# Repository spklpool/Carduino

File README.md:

# Carduino

This repository contains the source code for the Carduino library for Arduino IDE as well as design files for the electronics and the 3d printed enclosure for the Carduino device.  Each of these 3 components will be desctibed separately below.  More information about Carduino can be found at https://carduino.co

Everything you need to build a Carduino is in this repository if you have the necessary equipment.  If you are so inclined, you scan shop around for all the parts and build one yourself using the information you find in here.  You can also order a kit with all the electronic parts from our store at
https://www.tindie.com/stores/Sparkle/

There, you can also order one fully assembled and tested, including the 3d printed enclosure and a USB cable for close to the same price it would cost you to buy all the individual parts and the shipping costs.  Also, buying from our store helps support the continuing development of the project.  We have other things in the works you might like if you're interested in Cardano and electronics.

## Arduino library
The Arduino IDE can be downloaded here:
https://www.arduino.cc/en/software
The files that make up the library are under the src folder for reference if you want to look at the code.  To use it though, you'll want to install it as a library in the IDE.  Instructions for installing the library and everything else you need to program your Carduino can be found in this tutorial video:
https://www.youtube.com/watch?v=BPkC6jxjeJc&t=7s

## PCB design files
The PCB is designed using Eagle.  It meets the criteria for being edited using the free edition for personal use, which can be downloaded here:
https://www.autodesk.ca/en/products/eagle/free-download
The PCB design files can be found in the eagle folder.
The parts list with recommended manufacturer part numbers is available in the [parts file](eagle/parts.md)

## Enclosure 3d model
The enclosure was designed with TinkerCad.  Unfortunately, TimcarCad does not support saving the native files, but the exported .stl files can be imported and tweaked as you wish at:
https://www.tinkercad.com/
The 3d model files can be found in the model folder.

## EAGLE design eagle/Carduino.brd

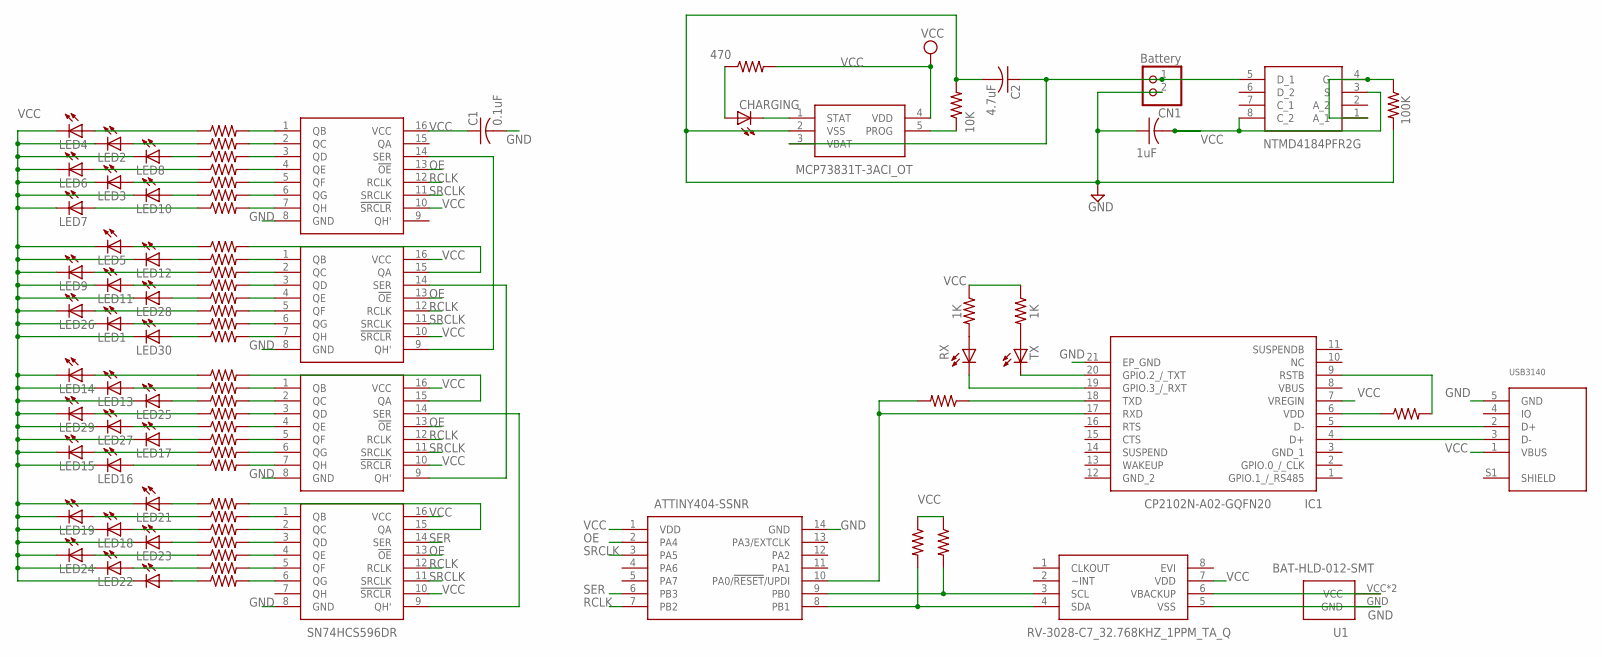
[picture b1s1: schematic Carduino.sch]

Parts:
C1: 0.1uF; C1206
C2: 4.7uF; C1206
C3: 1uF; C1206
CHARGING: Red; CHIP-LED0805
CN1: Battery; JST-PH-2-SMT-RA
IC1: CP2102N-A02-GQFN20; CP2102NA02GQFN20
IC3, IC4, IC5, IC6: SN74HCS596DR; SOIC127P600X175-16N
IC7: NTMD4184PFR2G; SOIC127P600X175-8N
IC8: ATTINY404-SSNR; SOIC127P600X175-14N
IC9: MCP73831T-3ACI_OT; SOT95P270X145-5N
IC11: RV-3028-C7_32.768KHZ_1PPM_TA_Q; RV3028C732768KHZ1PPMTAQC
LED1, LED2, LED3, LED4, LED5, LED6, LED7, LED8, LED9, LED10, LED11, LED12, LED13, LED14, LED15, LED16, LED17, LED18, LED19, LED20, LED21, LED22, LED23, LED24, LED25, LED26, LED27, LED28, LED29, LED30: LUXEON2835L128-1890NA3500001; LUXEON2835
R1, R16: 470; R0805
R2, R3, R7, R8, R9, R10, R11, R12, R13, R14, R15, R17, R18, R19, R20, R23, R31, R32, R33, R34, R35, R36, R37, R38, R39, R40, R41, R42, R43, R44, R45, R46, R47: 1K; R0805
R4, R5: 4.7K; R0805
R21: 100K; R0805
R22: 10K; R0805
RX: Green; CHIP-LED0805
TX: Red; CHIP-LED0805
U1: BAT-HLD-012-SMT; BATHLD012SMT
U$5: USB3140; USB3140-30-0170-0-C

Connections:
GND: C1.2, C2.2, C3.1, CN1.2 (1), IC1.21 (EP_GND), IC3.8 (GND), IC4.8 (GND), IC5.8 (GND), IC6.8 (GND), IC8.14 (GND), IC9.2 (VSS), IC11.5 (VSS), R21.2, R22.2, U1.GND, U$5.5 (GND)
unnamed: LED4.ANODE (A), R15.1
unnamed: LED2.ANODE (A), R14.1
unnamed: LED8.ANODE (A), R13.1
unnamed: LED6.ANODE (A), R12.1
unnamed: LED3.ANODE (A), R11.1
unnamed: LED12.ANODE (A), R7.1
unnamed: LED7.ANODE (A), R9.1
unnamed: LED5.ANODE (A), R8.1
unnamed: LED10.ANODE (A), R10.1
unnamed: LED9.ANODE (A), R17.1
unnamed: LED11.ANODE (A), R18.1
unnamed: LED28.ANODE (A), R19.1
unnamed: LED26.ANODE (A), R20.1
unnamed: LED1.ANODE (A), R31.1
unnamed: LED30.ANODE (A), R32.1
unnamed: LED14.ANODE (A), R33.1
unnamed: LED13.ANODE (A), R34.1
unnamed: LED25.ANODE (A), R35.1
unnamed: LED29.ANODE (A), R36.1
unnamed: LED27.ANODE (A), R37.1
unnamed: LED17.ANODE (A), R38.1
unnamed: LED15.ANODE (A), R39.1
unnamed: LED16.ANODE (A), R40.1
unnamed: LED21.ANODE (A), R41.1
unnamed: LED19.ANODE (A), R42.1
unnamed: LED18.ANODE (A), R43.1
unnamed: LED23.ANODE (A), R44.1
unnamed: LED24.ANODE (A), R45.1
unnamed: LED22.ANODE (A), R46.1
unnamed: LED20.ANODE (A), R47.1
unnamed: IC8.8 (PB1), IC11.4 (SDA), R4.2
unnamed: IC8.9 (PB0), IC11.3 (SCL), R5.2
unnamed: IC11.6 (VBACKUP), U1.VCC, U1.VCC2 (VCC)
unnamed: IC7.1 (A_1), IC7.4 (G), R21.1
unnamed: IC9.5 (PROG), R22.1
unnamed: C2.1, CN1.1 (2), IC7.5 (D_1), IC9.3 (VBAT)
unnamed: CHARGING.C, IC9.1 (STAT)
unnamed: CHARGING.A, R16.1
unnamed: IC1.20 (GPIO.2_/_TXT), TX.C
unnamed: IC1.19 (GPIO.3_/_RXT), RX.C
unnamed: IC1.18 (TXD), R1.1
unnamed: IC1.6 (VDD), R23.1
unnamed: IC1.9 (RSTB), R23.2
unnamed: IC3.1 (QB), R15.2
unnamed: IC3.2 (QC), R14.2
unnamed: IC3.3 (QD), R13.2
unnamed: IC3.4 (QE), R12.2
unnamed: IC3.5 (QF), R11.2
unnamed: IC3.6 (QG), R10.2
unnamed: IC3.7 (QH), R9.2
unnamed: IC4.15 (QA), R8.2
unnamed: IC4.1 (QB), R7.2
unnamed: IC4.2 (QC), R17.2
unnamed: IC4.3 (QD), R18.2
unnamed: IC4.4 (QE), R19.2
unnamed: IC4.5 (QF), R20.2
unnamed: IC4.6 (QG), R31.2
unnamed: IC4.7 (QH), R32.2
unnamed: IC5.15 (QA), R33.2
unnamed: IC5.1 (QB), R34.2
unnamed: IC5.2 (QC), R35.2
unnamed: IC5.3 (QD), R36.2
unnamed: IC5.4 (QE), R37.2
unnamed: IC5.5 (QF), R38.2
unnamed: IC5.6 (QG), R39.2
unnamed: IC5.7 (QH), R40.2
unnamed: IC6.6 (QG), R47.2
unnamed: IC6.5 (QF), R46.2
unnamed: IC6.4 (QE), R45.2
unnamed: IC6.3 (QD), R44.2
unnamed: IC6.2 (QC), R43.2
unnamed: IC6.1 (QB), R42.2
unnamed: IC6.15 (QA), R41.2
unnamed: IC5.14 (SER), IC6.9 (QH')
unnamed: IC4.14 (SER), IC5.9 (QH')
unnamed: IC3.14 (SER), IC4.9 (QH')
unnamed: IC1.5 (D-), U$5.2 (D+)
unnamed: IC1.4 (D+), U$5.3 (D-)
unnamed: IC1.17 (RXD), IC8.10 (PA0/!RESET!/UPDI), R1.2
unnamed: R2.2, RX.A
unnamed: R3.2, TX.A
OE: IC3.13 (!OE), IC4.13 (!OE), IC5.13 (!OE), IC6.13 (!OE), IC8.2 (PA4)
RCLK: IC3.12 (RCLK), IC4.12 (RCLK), IC5.12 (RCLK), IC6.12 (RCLK), IC8.7 (PB2)
SER: IC6.14 (SER), IC8.6 (PB3)
SRCLK: IC3.11 (SRCLK), IC4.11 (SRCLK), IC5.11 (SRCLK), IC6.11 (SRCLK), IC8.3 (PA5)
VCC: C1.1, C3.2, IC1.7 (VREGIN), IC3.10 (!SRCLR), IC3.16 (VCC), IC4.10 (!SRCLR), IC4.16 (VCC), IC5.10 (!SRCLR), IC5.16 (VCC), IC6.10 (!SRCLR), IC6.16 (VCC), IC7.3 (S), IC7.8 (C_2), IC8.1 (VDD), IC9.4 (VDD), IC11.7 (VDD), LED1.CATHODE (C), LED2.CATHODE (C), LED3.CATHODE (C), LED4.CATHODE (C), LED5.CATHODE (C), LED6.CATHODE (C), LED7.CATHODE (C), LED8.CATHODE (C), LED9.CATHODE (C), LED10.CATHODE (C), LED11.CATHODE (C), LED12.CATHODE (C), LED13.CATHODE (C), LED14.CATHODE (C), LED15.CATHODE (C), LED16.CATHODE (C), LED17.CATHODE (C), LED18.CATHODE (C), LED19.CATHODE (C), LED20.CATHODE (C), LED21.CATHODE (C), LED22.CATHODE (C), LED23.CATHODE (C), LED24.CATHODE (C), LED25.CATHODE (C), LED26.CATHODE (C), LED27.CATHODE (C), LED28.CATHODE (C), LED29.CATHODE (C), LED30.CATHODE (C), R2.1, R3.1, R4.1, R5.1, R16.2, U$5.1 (VBUS)

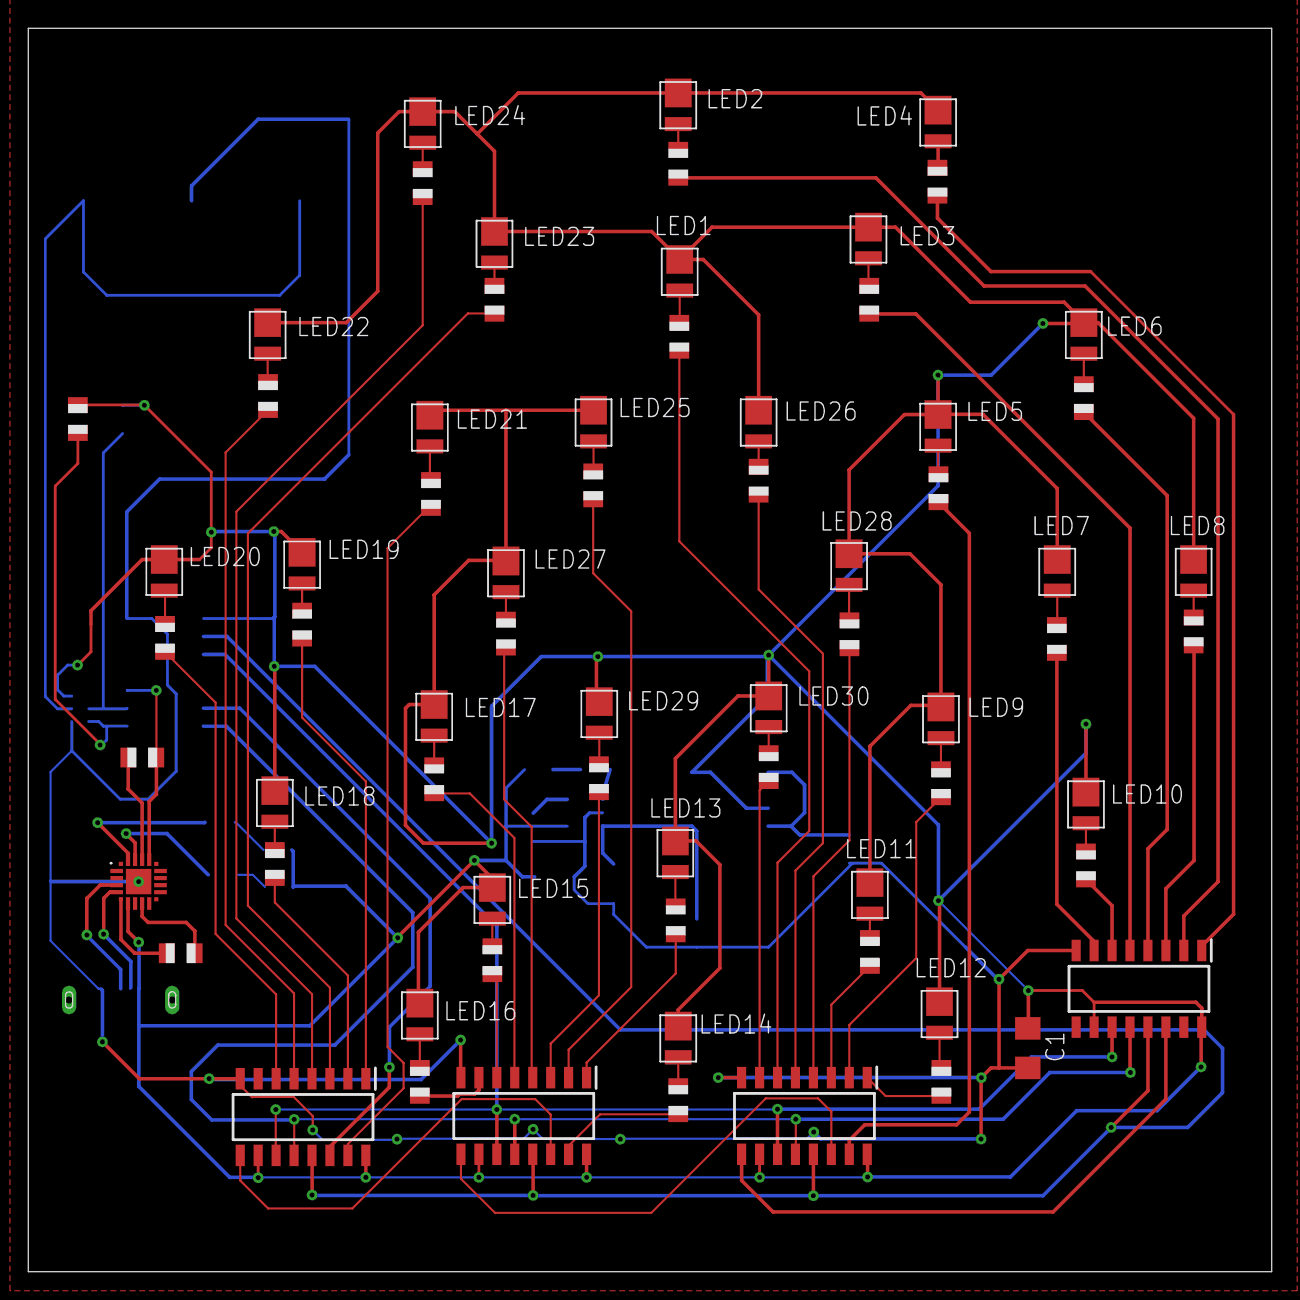
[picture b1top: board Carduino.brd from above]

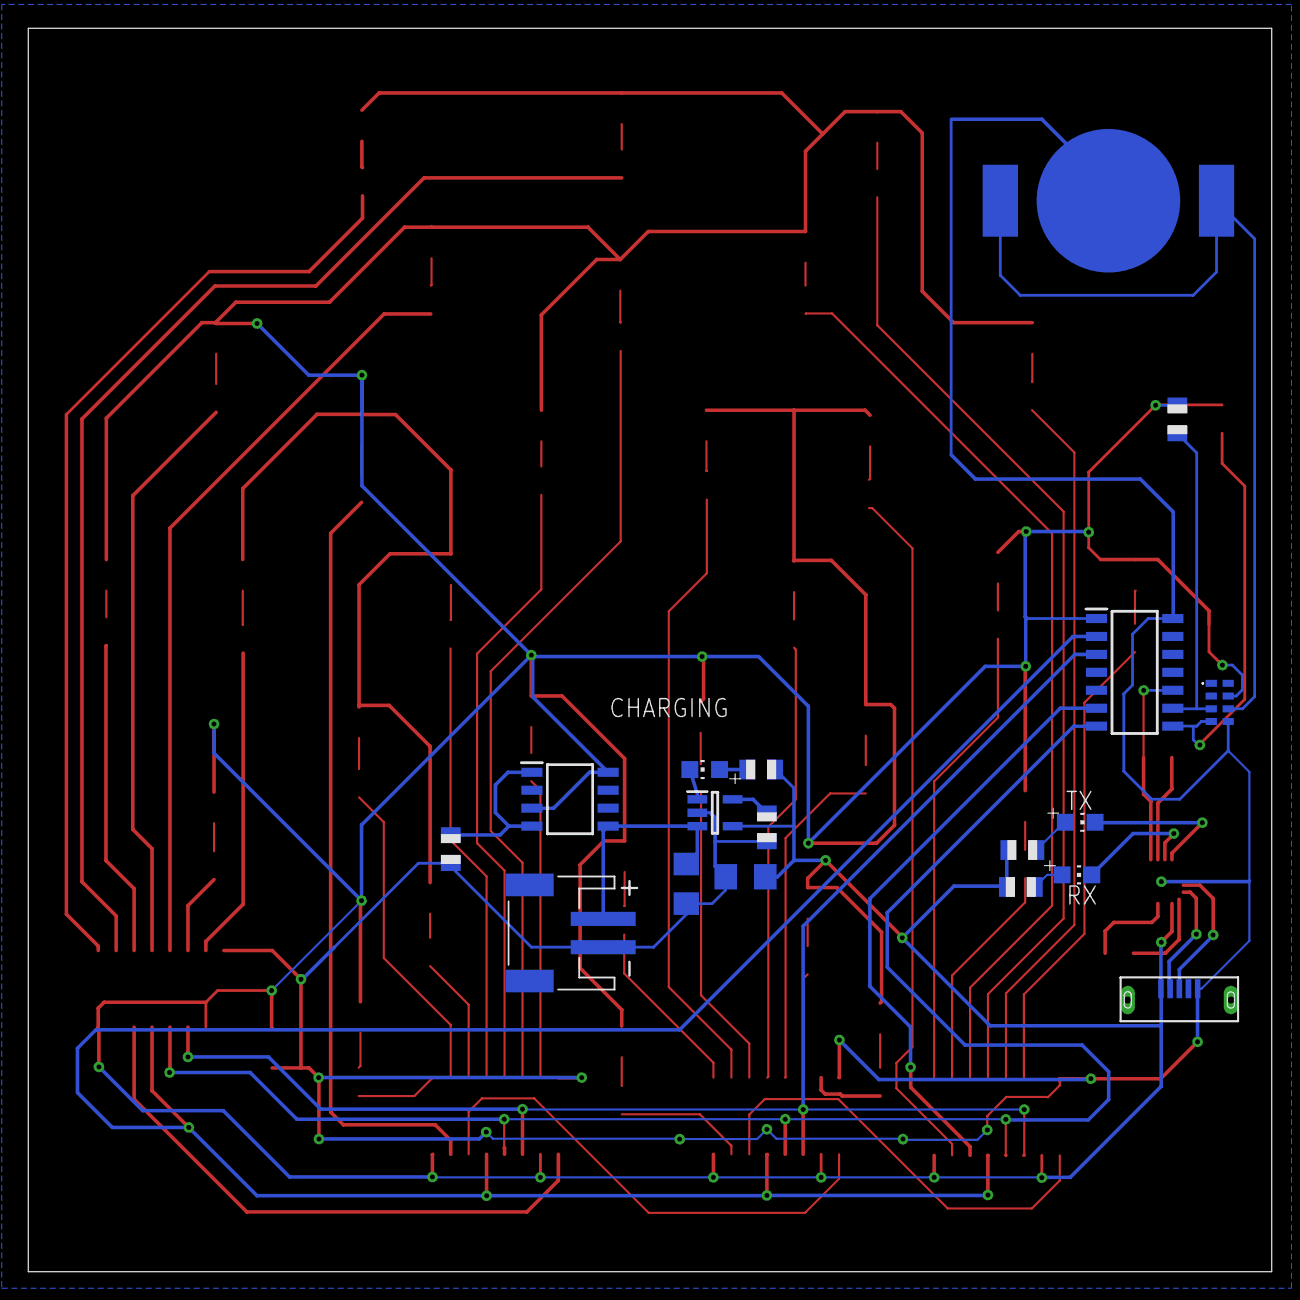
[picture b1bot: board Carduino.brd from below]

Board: 2 copper layers, 88.0 x 88.0 mm, 87 parts (18 on the bottom side), 87 nets.

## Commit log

2021-12-21 initial implementation
2021-12-21 real clock code
2021-12-21 initial library
2021-12-21 addin eagle files
2021-12-23 added logo and moved USB port
2021-12-23 cleaning up status
2021-12-23 start epoch count at 0
2022-01-03 added realtime clock
2022-01-14 better use of button to adjust dots
2022-01-16 attempt at true epoch time
2022-02-12 preparing for 1.1 release
2022-02-12 starting documentation
2022-03-06 removing dimensions that got into the board
2022-03-06 oe pin and teaser eye candy
2022-03-06 enclosure 3d model files
2022-03-06 adding brightness control
2022-03-06 more examples
2022-03-06 preparing for 1.0.1 release
2022-03-08 removing file that was breaking examples
2022-03-08 fixed compile warnings
2022-03-08 bumping up version
2022-03-09 new clock and ftdi chips
2022-03-18 more sturdy model
2022-04-03 support for RV-3028-C7 RTC
2022-04-03 make enclosure less fragile
2022-04-03 new clock with old ftdi
2022-04-03 less expensive RTC with existing ftdi chip
2022-04-03 bumping up version for next release
2022-04-04 parts list
2022-04-04 link to parts file
2022-04-04 store plug
2022-04-04 adding missing capacitor to parts list
2022-04-10 Updating microcontroller
2022-04-11 link to programming tutorial video in readme
2022-04-18 swaping ftdi chip with CP2102N
2022-11-12 support for setting time from different time zones
